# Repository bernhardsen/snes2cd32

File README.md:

# SNES2CD32 Adapter
This is a hobby project of mine that was never 100% completed, but it works for the most part in its current state.
`board` director contains the eagle files to create the PCB, and schematics with parts.
There are two current "bugs" with the PCB:
- pin 11 on IC1 should be pulled high through a 10k resistor (it's currently not connected)
- The two resistors on each side of C5 should be connected to VCC instead of GND

The chip used is an atmega8, and you need to put the arduino bootloader on it before transfering the firmware.

## Usage

To use the controller normally, just plug in the controller and you’re good.

### Re-map up/down
Most Amiga games would have you press up to jump. This is awkward and weird, even more so on a joypad. To remap up to a different button do the following:
1.  Press SELECT to enter configuration mode.
2.  Press UP to specify you want to remap UP, or DOWN if you want to remap DOWN.
3.  Press the button you want to swap with (A, B, X, Y, L or R).

### Turbo fire
You can enable turbo fire on A, B, X, Y, L and/or R, by doing the following:
1.  Press SELECT to enter configuration mode.
2.  Press START to specify you want to configure turbo fire.
3.  Press and hold the buttons you want to enable turbo fire on, and while holding them, press SELECT to confirm.

### Record/Playback macro
You can record a macro and have the controller automatically replay the inputs.

To start recording press SELECT, then L to specify you want to record a macro. The macro start recording on the next button press. It records until you press SELECT again, or the memory is full. The memory can fit around 50 button presses.

To play back a macro, press SELECT then R. The controller is not usable until the macro is done. Press SELECT while the macro is running to abort.

Timing is not 100% consistant in the current firmware.

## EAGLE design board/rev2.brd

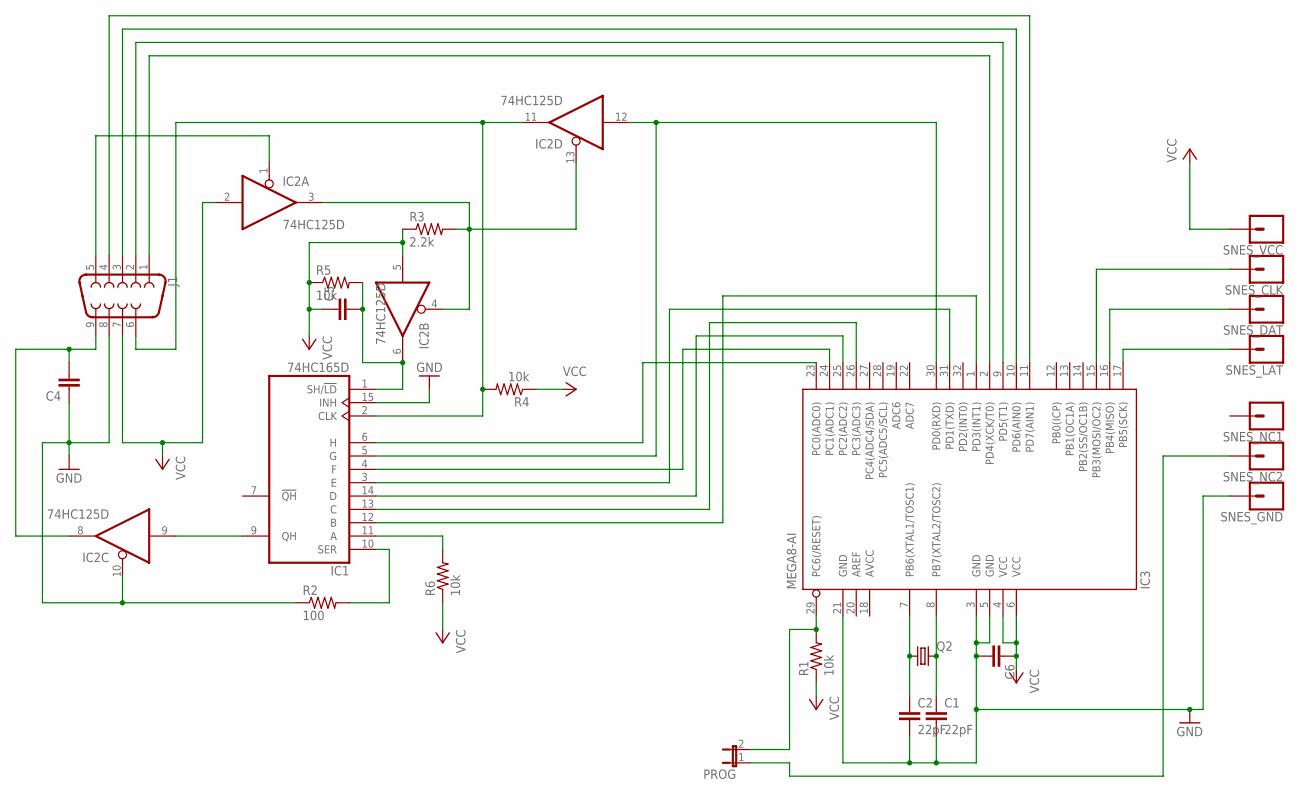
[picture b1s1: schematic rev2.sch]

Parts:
C1, C2: 22pF; C1206
C4, C5, C6: C-EUC1206; C1206
IC1: 74HC165D; SO16
IC2: 74HC125D; SO14
IC3: MEGA8-AI; TQFP32-08
J1: DB9FEMALE; DB9
PROG: JP1E; JP1
Q2: CRYSTALHC49S; HC49/S
R1, R4, R5, R6: 10k; R1206
R2: 100; R1206
R3: 2.2k; R1206
SNES_CLK: CONN_01PTH_2MM; 1X01_2MM
SNES_DAT: CONN_01PTH_2MM; 1X01_2MM
SNES_GND: CONN_01PTH_2MM; 1X01_2MM
SNES_LAT: CONN_01PTH_2MM; 1X01_2MM
SNES_NC1, SNES_NC2: CONN_01PTH_2MM; 1X01_2MM
SNES_VCC: CONN_01PTH_2MM; 1X01_2MM

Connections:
AVCC: IC3.18 (AVCC)
GND: C1.2, C2.2, C4.1, C6.2, IC1.8 (GND), IC1.15 (INH), IC2.7 (GND), IC2.10 (OE), IC3.3 (GND), IC3.5 (GND), IC3.21 (GND), J1.8, R2.1, SNES_GND.1
unnamed: IC3.17 (PB5(SCK)), SNES_LAT.1
unnamed: IC3.16 (PB4(MISO)), SNES_DAT.1
unnamed: IC3.15 (PB3(MOSI/OC2)), SNES_CLK.1
unnamed: C2.1, IC3.7 (PB6(XTAL1/TOSC1)), Q2.1
unnamed: C1.1, IC3.8 (PB7(XTAL2/TOSC2)), Q2.2
unnamed: IC3.29 (PC6(/RESET)), PROG.2, R1.2
unnamed: IC3.11 (PD7(AIN1)), J1.4
unnamed: IC3.10 (PD6(AIN0)), J1.3
unnamed: IC3.9 (PD5(T1)), J1.2
unnamed: IC3.2 (PD4(XCK/T0)), J1.1
unnamed: C4.2, IC2.8 (O), J1.9
unnamed: IC1.9 (QH), IC2.9 (I)
unnamed: IC2.1 (OE), J1.5
unnamed: IC1.10 (SER), R2.2
unnamed: C5.2, IC1.1 (SH/!LD), IC2.6 (O), R5.2
unnamed: IC2.3 (O), IC2.4 (OE), IC2.13 (OE), R3.2
unnamed: IC1.2 (CLK), IC2.11 (O), J1.6, R4.2
unnamed: PROG.1, SNES_NC2.1
unnamed: IC1.12 (B), IC3.1 (PD3(INT1))
unnamed: IC1.14 (D), IC3.25 (PC2(ADC2))
unnamed: IC1.13 (C), IC3.26 (PC3(ADC3))
unnamed: IC1.6 (H), IC3.23 (PC0(ADC0))
unnamed: IC1.4 (F), IC3.24 (PC1(ADC1))
unnamed: IC1.3 (E), IC3.31 (PD1(TXD))
unnamed: IC1.5 (G), IC2.12 (I), IC3.30 (PD0(RXD))
unnamed: IC1.11 (A), R6.2
VCC: C5.1, C6.1, IC1.16 (VCC), IC2.2 (I), IC2.5 (I), IC2.14 (VCC), IC3.4 (VCC), IC3.6 (VCC), J1.7, R1.1, R3.1, R4.1, R5.1, R6.1, SNES_VCC.1

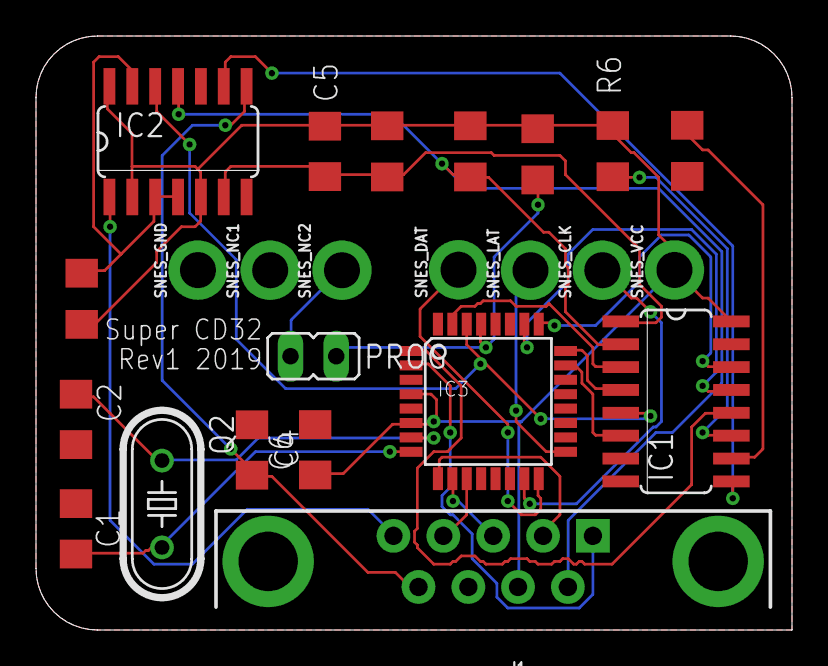
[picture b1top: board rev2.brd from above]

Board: 2 copper layers, 42.0 x 33.0 mm, 24 parts (0 on the bottom side), 28 nets.

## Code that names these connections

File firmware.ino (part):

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byte macroMem[256];

void setup() {
  DDRB =  B00101000; // PB3 and PB5 as output, the rest as input // + PB0 (status LED)
  DDRC |= B00001111; // Set PC0 - PC3 as outputs
  DDRD |= B11111111; // Set all of PORTD to output

  PORTB |= B00001000; // Set clock high
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void readController() {
  int i;
  
  PORTB |= B00100000; // write 1 to PB5
  delayMicroseconds(12); // This delay could maybe be used to do other things, maybe do some logic and wait less
  PORTB &= B11011111; // write 0 to PB5
  delayMicroseconds(6);

  cState1 = 0x00;
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    if (PINB & 0x10) {
      cState1 |= 1 << i;
    }
    PORTB &= B11110111; // write 0 to PB3
    delayMicroseconds(6);
    PORTB |= B00001000; // write 1 to PB3
    delayMicroseconds(6);
  }
  
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    if (PINB & 0x10) {
      cState2 |= 1 << (i);
    }
    PORTB &= B11110111; // write 0 to PB3
    delayMicroseconds(6);
    PORTB |= B00001000; // write 1 to PB3
    delayMicroseconds(6);
  }
}
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

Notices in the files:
parts and their libraries:
SparkFun-Connectors: Licensing: Creative Commons ShareAlike 4.0 International - https://creativecommons.org/licenses/by-sa/4.0
